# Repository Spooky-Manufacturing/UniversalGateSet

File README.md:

# UniversalGateSet
The Universal Gate Set is SpookyMFG's open-hardware universal quantum gate specifications.

## What is a universal gate set?
A universal gate set is a set of logic gates that allow you to perform any theoretical quantum computation

## Gates Implemented
* Controlled-Z
* Measurement (Single-photon detector)

## Gates Planned
* Pauli-X
* Pauli-Y
* Pauli-Z
* Hadamard
* Nonlinear-Sign Shift Gate
* Controlled-X Gate
* Faint-Laser Single Photon Source

## Gate Sizes
* [ ] Macro - Built utilizing off-the-shelf optical components
* [ ] Micro - Discrete sized quantum logic gates
* [ ] Nano - Chip scale components

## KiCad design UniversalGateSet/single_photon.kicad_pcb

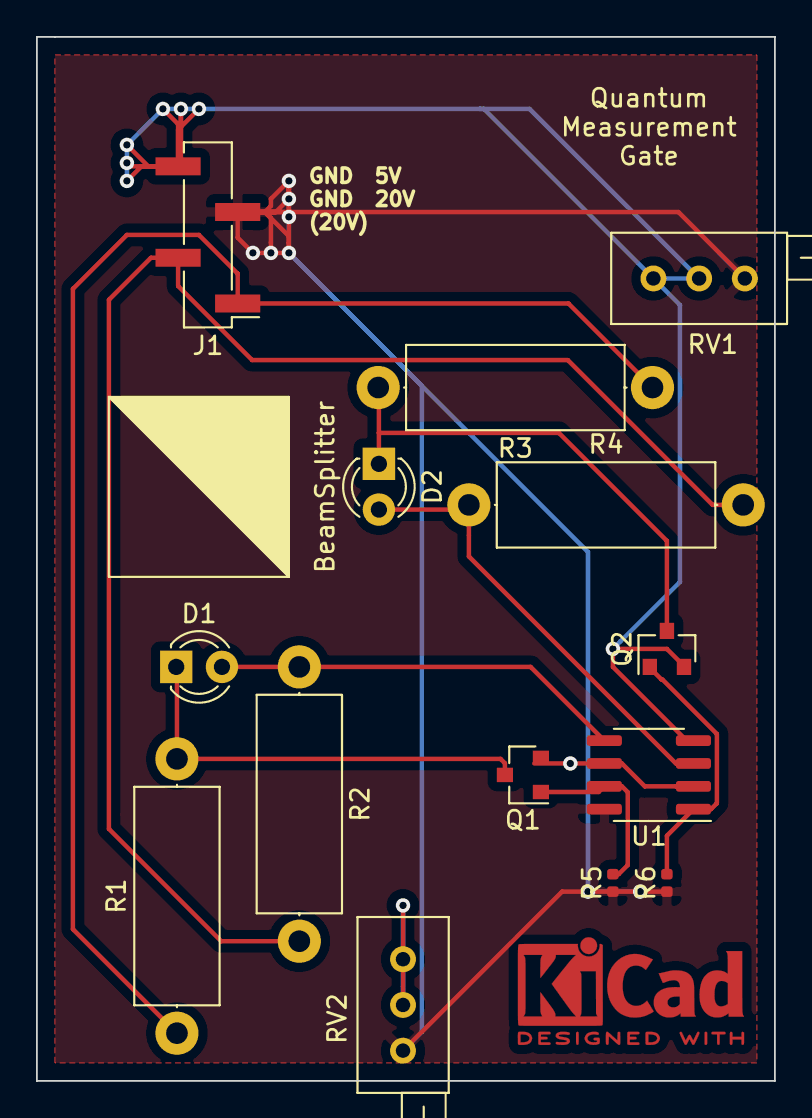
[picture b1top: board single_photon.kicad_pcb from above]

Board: 2 copper layers, 41.0 x 58.0 mm, 15 parts (0 on the bottom side), 10 nets.

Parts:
B1: BeamSplitter
D1, D2: SPAD; LED_D3.0mm_Clear
J1: Conn_01x04; PinHeader_1x04_P2.54mm_Vertical_SMD_Pin1Left
Q1, Q2: A03400A; SOT-23
R1, R3: 1k; R_Axial_DIN0414_L11.9mm_D4.5mm_P15.24mm_Horizontal
R2, R4: 3k; R_Axial_DIN0414_L11.9mm_D4.5mm_P15.24mm_Horizontal
R5, R6: 1k; R_0402_1005Metric
RV1, RV2: R_POT_TRIM_US; Potentiometer_Bourns_3296X_Horizontal
U1: LM393; SOIC-8_3.9x4.9mm_P1.27mm

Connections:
/5v: J1.3, R5.1, R6.1, RV1.3, RV2.3, U1.8
/20v: J1.1, R1.1, R3.1
/GND: J1.4, Q1.2, Q2.2, RV1.1, RV1.2, RV2.1, RV2.2, U1.2, U1.4, U1.6
/GND_20: J1.2, R2.2, R4.2
/H: D2.1, Q2.3, R3.2
/V: D1.1, Q1.3, R1.2
unnamed: D1.2, R2.1, U1.5
unnamed: D2.2, R4.1, U1.3
unnamed: Q1.1, R5.2, U1.7
unnamed: Q2.1, R6.2, U1.1

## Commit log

2022-03-26 modified: README.md new file: UniversalGateSet/CZ.sch new file: UniversalGateSet/UniversalGateSet-cache.lib new file: UniversalGateSet/UniversalGateSet.kicad_pcb new file: UniversalGateSet/UniversalG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
2022-03-26 Update README.md
    Control-Z gate was added, not Pauli-Z
